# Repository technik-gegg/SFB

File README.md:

# Welcome to the SFB project

This is the firmware for the **S**mart **F**ilament **B**uffer as published on [Printables](https://www.printables.com/de/model/197621-smart-filament-buffer-2) and [Thangs](https://thangs.com/mythangs/file/58718).

The Smart Filament Buffer (used for multi-material 3D printing) comes with an integrated 5 fold filament run-out detector, which is based on the Arduino Nano and a bunch of linear Hall-Effect sensors.
An integrated I2C OLED makes reading the current status and it's configuration a breeze.

This project utilizes PlatformIO and VS-Code. Make sure you have those tools installed on your PC/Mac, open the project in VS-Code, build it, flash it onto the Arduino Nano and you're all set to go.

The schematic for this project is pretty simple and straight forward:

All the electronics will fit onto a standard 60x40 mm prototype board.

If you don't feel like wiring all this up on a prototype board by hand, head over to my [PCB repository at AISLER](https://aisler.net/technik-gegg/smuff/sfb-pcb) where you can comfortably order one or more PCB(s) right away. Usually, you will get your PCB made and delivered within 7 (work) days.

<figure>
    
    <figcaption>Assembled PCB, with courtesy of maker Defenc</figcaption>
</figure>

Beside the Arduino Nano, the OLED and sensors, you have 3 push buttons, labelled *PREV*, *MENU* and *NEXT*, to handle the integrated menus.
Connector J1 is being used to attach the SFB to your 3D printer, which will supply the power to the SFB on pins 1 and 2 (GND/+5V).
Pin 3 (SIG) is used to connect the run-out signal to the E-STOP header on your 3D printer controller, which becomes HIGH (+5V) as soon as a run-out is triggered.

Configured correctly, this run-out signal will cause your 3D Printer to pause the print before it starts printing hot air.

On a Duet3D controller board for example, you'll need to add these two lines of GCode in your *config.g*:

```Gcode
M591 D0 P2 C2 S1        ; Set filament sensing sensor to switch (active high)
M581 E0 T1 S1 C1        ; Configure external trigger to pause the print only when printing
```

Klipper in contrast requires you to configure the according pin of the "runout_sensor" in your *printer.cfg* file, i.e. pin GPIO16, active high:

```Python
[filament_switch_sensor runout_sensor]
switch_pin: gpio16
pause_on_runout: True
```

In Marlin you'll need to enable and set up the run-out sensor in your *Configuration.h* file, compile and flash the new firmware. For example: Pin PA15, active high:

```Arduino
#define FILAMENT_RUNOUT_SENSOR
#if ENABLED(FILAMENT_RUNOUT_SENSOR)
  #define FIL_RUNOUT_ENABLED_DEFAULT true    // Enable the sensor on startup. Override with M412 followed by M500.
  #define NUM_RUNOUT_SENSORS   1             // Number of sensors, up to one per extruder. Define a FIL_RUNOUT#_PIN for each.
  
  #define FIL_RUNOUT1_PIN      PA15          // Depends on your controller board!
  #define FIL_RUNOUT1_STATE    HIGH          // Pin state indicating that filament is NOT present.
  #define FIL_RUNOUT1_PULLDOWN               // Use internal pulldown for filament runout pins.
  ...
#endif
```

Pin 4 (RX) and Pin 5 (TX) of J1 are routed to the Arduino Nano serial port, which can be used to command the SFB to monitor a specific tool only. If none is set (T= -1), all sensors are monitored and the run-out triggers as soon as no sensor reports detecting "filament loaded".
Ideally, this communication path is wired to your controller (either your 3D printer or the SMuFF) in order to set up the tool to monitor automatically during a print.

# Calibration

Before the SFB is ready to use, you'll need to calibrate it. Therefore, press the *MENU* button to open the main menu and select the item **Sensors**. The SFB will print the current sensor values on the display. Take care that, as long as no filaments are loaded, all sensors are within the same value range (+-20 Gs).
If one or more of the sensors show a negative value while all others show positive values, you have to flip the magnets - of those showing negatives - upside-down.
Once you push against the steel ball of one of the sensors, the sensor readout will raise towards the max. value of 640 (Gs). This way you're able to check whether all sensors are working correctly.
Once all sensors are in the same (lower) range, press the **PREV** button to start the calibration sampling. After the sampling is done, the SFB will show the min./max. Gauss values at the very bottom of the display.
Now press the **NEXT** button in order to store these values in EEPROM and the calibration is done.

# Run-out detection

In "simple mode", the run-out detection does not need to know which filament is currently in use. It will monitor all sensors continously and as soon as all of them are below the threshold (1.75 times the calibrated min. Gauss value), it'll start the run-out countdown after which the run-out is signaled.
If one of the sensors gets triggered while the countdown is running, the countdown will be interrupted and the counter reset. This behaviour is needed for retractions and/or tool changes.
Via the integrated menu **Trigger**, you're able to change the countdown timespan (15 to 120 seconds), which gets stored in the Arduinos EEPROM.

In "control mode" (means: your SFB is connected to either the SMuFFs or the 3D printers TTL serial interface via the *RX* pin), the SFB will monitor the run-out for the requested tool only, which is set after a **Tn** command has been received (n = tool number). All other sensors will be ignored and also not drawn onto the display.
This stays valid until the tool is being reset by a **T-1** command, which basically instructs the SFB to return to "simple mode". *Please notice: Once a tool has been set, it'll be stored in the EEPROM, so that the current tool will stay active even after the SFB has been reset*

# Daisy-Chaining SFBs

Daisy-Chaining SFB devices allows you to handle more than 5 tools/filaments (up to 20).
In order to use this feature, you need to add a wire from the **SIG** output of the next device to pin **TX** of the current device, set it to **Chained**/**Last** in the settings menu **Mode** and assign an ID in settings menu **Device** (according to the picture below). **Chained** means there is yet another device in the chain sending a run-out signal, **Last** means this is the very last device in the chain.

In Daisy-Chain mode only the first (0: 1st) SFB will pass the run-out signal to the 3D Printer, which follows the same strategy as with one SFB in "normal" mode, whereas the "last" device will initiate the run-out countdown.
Also, numbering of the tools will be set according to the device IDs, i.e. T0-T4 on *1st*, T5-T9 on *2nd*, T10-T14 on *3rd*.

**Please keep in mind:**

+ In Daisy-Chain mode the *TX* pin of the SFB will be detached internally and thus, it won't be able to send any data back to the controller. Though, you're still able to send *Tn* commands from the controller to the device.
+ *For flashing the firmware you **must** detach the connector from J1.*
+ All devices need to be powered with +5V/GND from the same source.
+ In order to use the tool select feature (monitoring only one sensor) all devices must be able to receive the according command via the *RX* pin. This may require adding an external driver IC (i.e. [SN74LS126A](https://www.ti.com/lit/ds/symlink/sn74ls126a.pdf) or similar) between the *TX* wire of the senders serial interface and the *RX* input of the SFBs if you encounter the SFBs aren't reacting to the T*n* commands.

# Credits

A shout-out goes to [Oliver Kraus]( https://github.com/olikraus/U8G2_Arduino) for his amazing U8G2 display library and [Albert van Dalen](https://github.com/avandalen/avdweb_AnalogReadFast) for his fast analog library.

# Recent changes

### 2022-08-10

+ overhauled this README
+ added overflow prevention while setting the run-out timer.
+ added [Albert van Dalen's library](https://github.com/avandalen/avdweb_AnalogReadFast) for a faster read out of the Hall sensor values.
+ added option to show the *Info* screen when pressing the **PREV** button in main screen.
+ added option to show the *Sensors* screen when pressing the **NEXT** button in main screen.
+ added configurable rotation of the tool names (T*n*) on the main screen for better readability in different orientations of the SFB. Everything else stays in Portrait mode.
+ prefixed debug messages with "echo:" to not spam the 3D printer controller.

### 2022-08-08

+ status display on startup (reset) will show the current Mode and device ID.
+ renamed menu item *Defaults* to *\*Reset\** because it fits better and makes more sense actually.
+ added Daisy-Chain mode, which allows you to "chain up" multiple SFBs to one virutally bigger unit.

### 2022-08-06

+ replaced the Full buffer of the OLED display with Page buffers because the Arduino ran into low memory issues. Refresh/drawing of the display will be a bit slower now.
+ added sending some debug messages to the serial port while the device is initializing.

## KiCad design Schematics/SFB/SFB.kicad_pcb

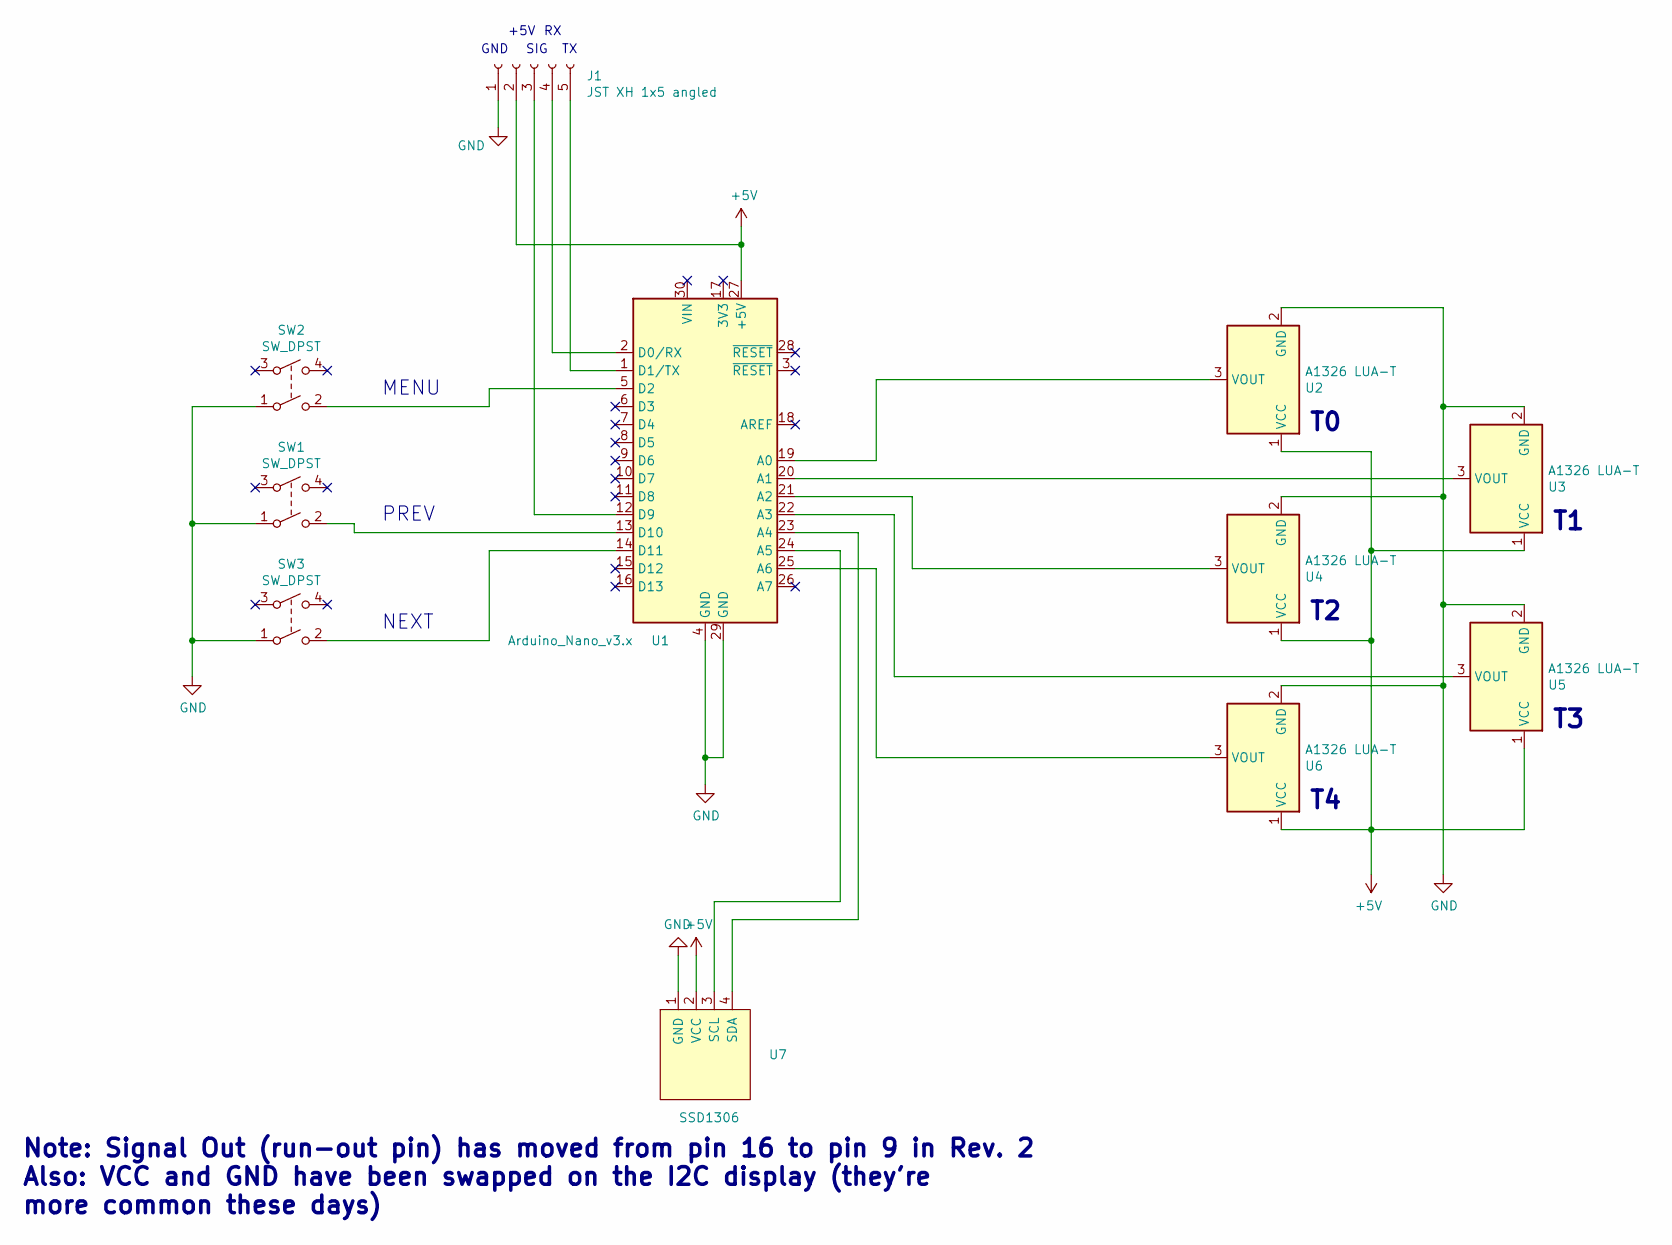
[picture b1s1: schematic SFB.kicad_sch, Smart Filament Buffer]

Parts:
J1: JST XH 1x5 angled; JST_XH_S5B-XH-A_1x05_P2.50mm_Horizontal
SW1, SW2, SW3: SW_DPST; SW_Tactile_Straight_KSA0Axx1LFTR-4Pin
U1: Arduino_Nano_v3.x; Arduino_Nano
U2, U3, U4, U5, U6: A1326 LUA-T; TO-92Flat
U7: SSD1306; PinHeader_1x04_P2.54mm_Vertical

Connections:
+5V: J1.2, U1.27 (+5V), U2.1 (VCC), U3.1 (VCC), U4.1 (VCC), U5.1 (VCC), U6.1 (VCC), U7.2 (VCC)
GND: J1.1, SW1.1, SW2.1, SW3.1, U1.4 (GND), U1.29 (GND), U2.2 (GND), U3.2 (GND), U4.2 (GND), U5.2 (GND), U6.2 (GND), U7.1 (GND)
unnamed: J1.3, U1.12 (D9)
unnamed: J1.4, U1.2 (D0/RX)
unnamed: J1.5, U1.1 (D1/TX)
unnamed: SW1.2, U1.13 (D10)
unnamed: SW2.2, U1.5 (D2)
unnamed: SW3.2, U1.14 (D11)
unnamed: U1.19 (A0), U2.3 (VOUT)
unnamed: U1.20 (A1), U3.3 (VOUT)
unnamed: U1.21 (A2), U4.3 (VOUT)
unnamed: U1.22 (A3), U5.3 (VOUT)
unnamed: U1.23 (A4), U7.4 (SDA)
unnamed: U1.24 (A5), U7.3 (SCL)
unnamed: U1.25 (A6), U6.3 (VOUT)

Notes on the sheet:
MENU
PREV
Note: Signal Out (run-out pin) has moved from pin 16 to pin 9 in Rev. 2 Also: VCC and GND have been swapped on the I2C display (they're more common these days)
GND
+5V
NEXT
SIG

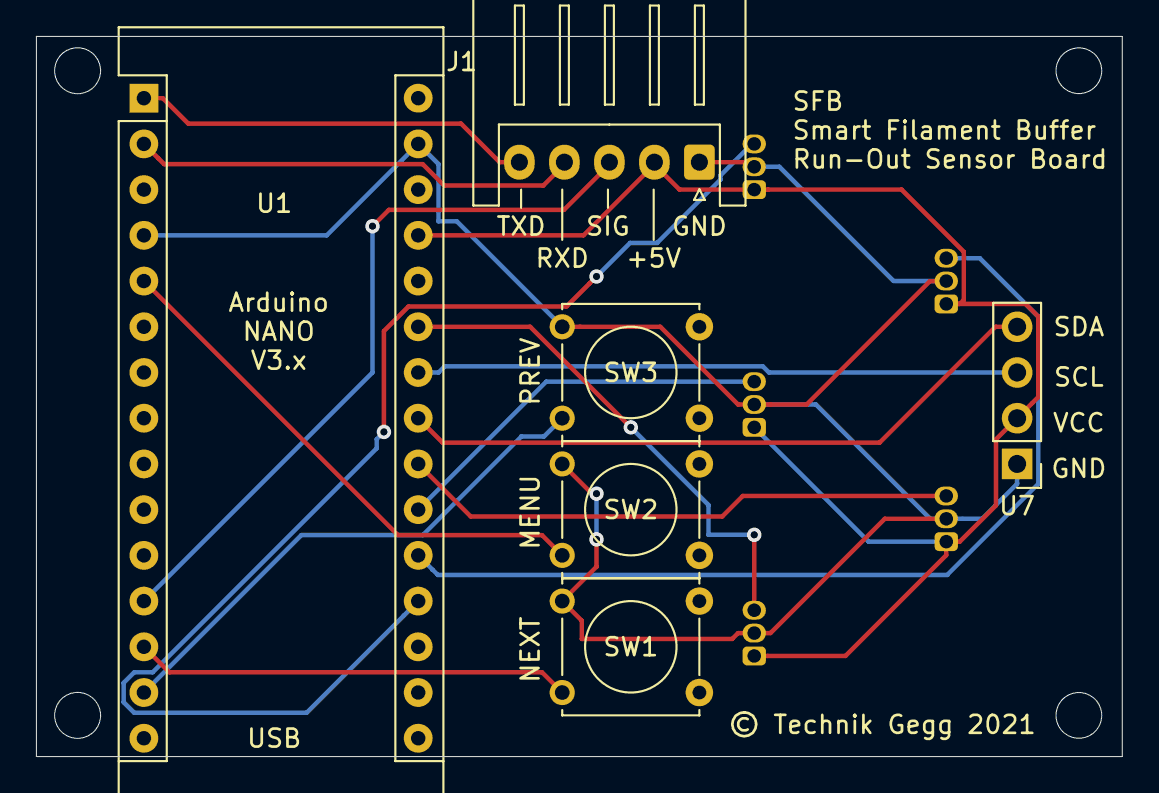
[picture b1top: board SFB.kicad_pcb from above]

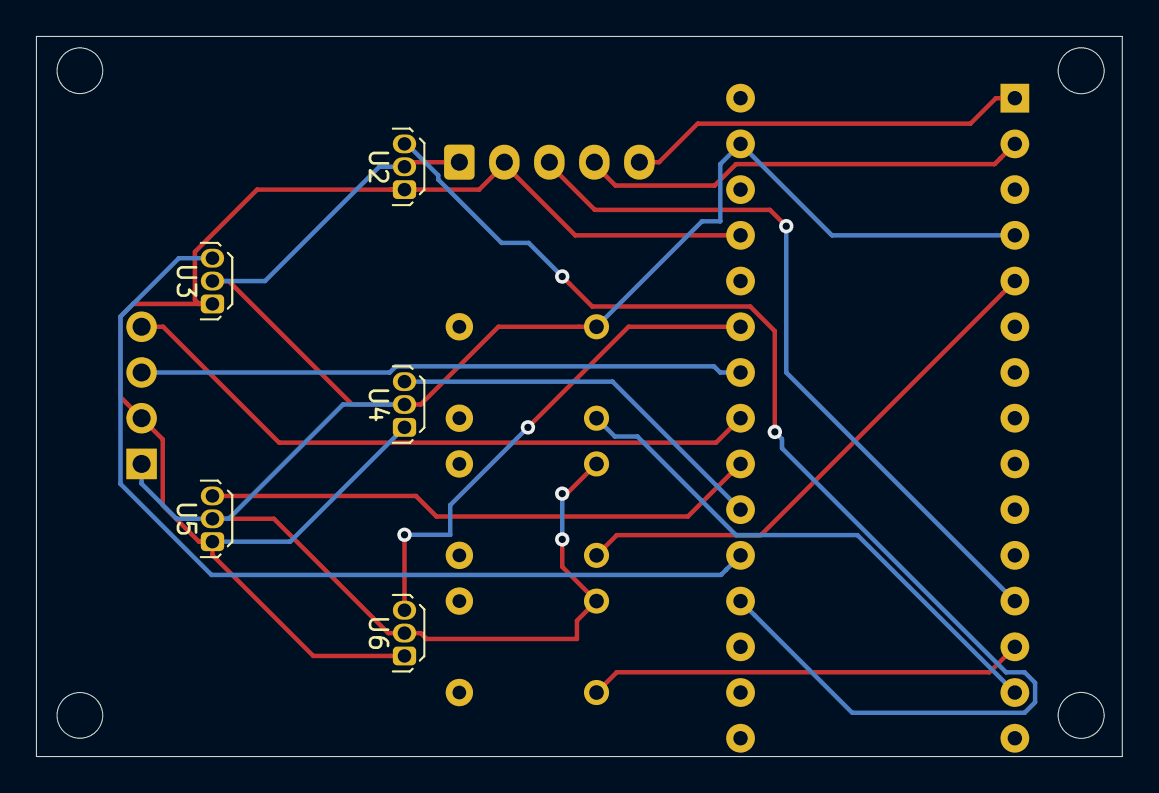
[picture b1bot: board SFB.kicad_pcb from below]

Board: 2 copper layers, 60.3 x 40.0 mm, 11 parts (5 on the bottom side), 15 nets.

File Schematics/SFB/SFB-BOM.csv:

"Source:","D:\Data\PlatformIO\SFB\SFB\Schematics\SFB\SFB.sch"
"Date:","02.08.2021 18:03:10"
"Tool:","Eeschema (5.1.2)-2"
"Component Count:","11"
"Ref","Value","Footprint","Datasheet","Manufacturer","Vendor"
"J1","JST XH 1x5 angled","Connector_JST:JST_XH_S5B-XH-A_1x05_P2.50mm_Horizontal","~","",""
"SW1","SW_DPST","SFB:SW_Tactile_Straight_KSA0Axx1LFTR-4Pin","~","",""
"SW2","SW_DPST","SFB:SW_Tactile_Straight_KSA0Axx1LFTR-4Pin","~","",""
"SW3","SW_DPST","SFB:SW_Tactile_Straight_KSA0Axx1LFTR-4Pin","~","",""
"U1","Arduino_Nano_v3.x","Module:Arduino_Nano","http://www.mouser.com/pdfdocs/Gravitech_Arduino_Nano3_0.pdf","",""
"U2","A1326 LUA-T","Package_TO_SOT_THT:TO-92Flat","http://www.allegromicro.com/~/media/Files/Datasheets/A1301-2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","",""
"U3","A1326 LUA-T","Package_TO_SOT_THT:TO-92Flat","http://www.allegromicro.com/~/media/Files/Datasheets/A1301-2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","",""
"U4","A1326 LUA-T","Package_TO_SOT_THT:TO-92Flat","http://www.allegromicro.com/~/media/Files/Datasheets/A1301-2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","",""
"U5","A1326 LUA-T","Package_TO_SOT_THT:TO-92Flat","http://www.allegromicro.com/~/media/Files/Datasheets/A1301-2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","",""
"U6","A1326 LUA-T","Package_TO_SOT_THT:TO-92Flat","http://www.allegromicro.com/~/media/Files/Datasheets/A1301-2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","",""
"U7","SSD1306","Connector_PinHeader_2.54mm:PinHeader_1x04_P2.54mm_Vertical","","",""

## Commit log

2019-06-25 Readme added
2021-07-24 Added Leonardo, Tool selection
2021-07-24 Updated gitignore
2021-07-28 Added PCB Rev.2 design
2021-07-31 Update README.md
    Link updated
2021-07-31 Update README.md
    Updated
2022-08-06 Updated; See README.md
2022-08-06 Corrected content
2022-08-06 Added link for ordering PCBs
2022-08-07 Added Daisy-Chaining; See README.md
2022-08-08 Reworked Daisy-Chain wiring; See README.md

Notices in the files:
Schematics/SFB/SFB.kicad_pcb:
© Technik Gegg 2021
